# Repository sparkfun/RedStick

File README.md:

**NOTE:** *This product has been retired from our catalog. If you are looking for more up-to-date info, please check out some of these resources to see how other users are still hacking and improving on this product.*
* *[SparkFun Forum](https://forum.sparkfun.com/)*
* *[Comments Here on GitHub](https://github.com/sparkfun/RedStick/issues)*

SparkFun RedStick
========================================

[*SparkFun RedStick (DEV-13741)*](https://www.sparkfun.com/products/13741)

A 328p micro board with boost regulator that runs at 16MHz and has a built in boost regulator for battery usage.

Spawned from the BadgerStick promo.

Repository Contents
-------------------

* **/Documentation** - Data sheets, additional product information
* **/Hardware** - Eagle design files (.brd, .sch)
* **/Production** - Production panel files (.brd)
* **/Software** - Related software for the RedStick

Documentation
--------------
* **[LED Array Library](https://github.com/sparkfun/SparkFun_LED_Array_8x7_Arduino_Library)** - Arduino LED Array library for the RedStick.
* **[Hookup Guide](https://learn.sparkfun.com/tutorials/redstick-hookup-guide)** - Basic hookup guide for the RedStick.
* **[SparkFun Fritzing repo](https://github.com/sparkfun/Fritzing_Parts)** - Fritzing diagrams for SparkFun products.
* **[SparkFun 3D Model repo](https://github.com/sparkfun/3D_Models)** - 3D models of SparkFun products. 

Version History
---------------
* [V_1.0](https://github.com/sparkfun/RedStick/tree/V_1.0) - Product release version

License Information
-------------------

This product is _**open source**_! 

Please review the LICENSE.md file for license information. 

If you have any questions or concerns on licensing, please contact techsupport@sparkfun.com.

Distributed as-is; no warranty is given.

- Your friends at SparkFun.

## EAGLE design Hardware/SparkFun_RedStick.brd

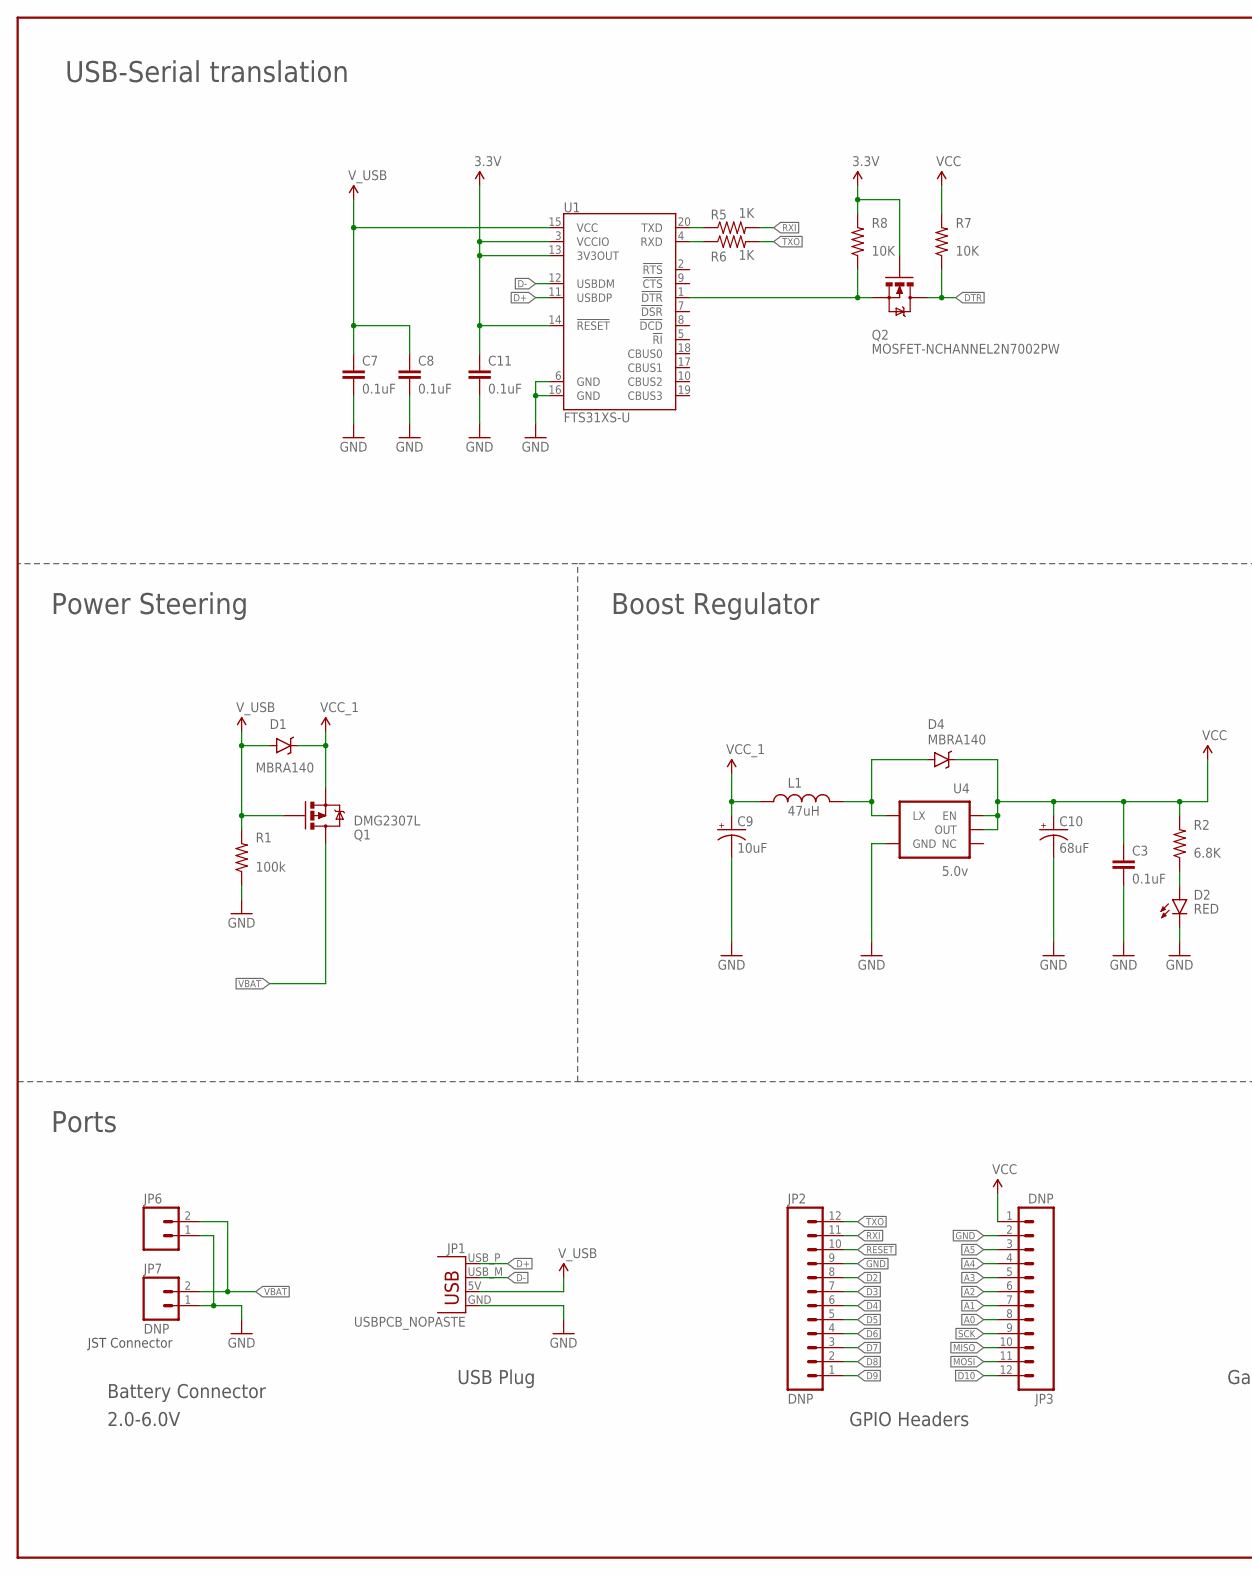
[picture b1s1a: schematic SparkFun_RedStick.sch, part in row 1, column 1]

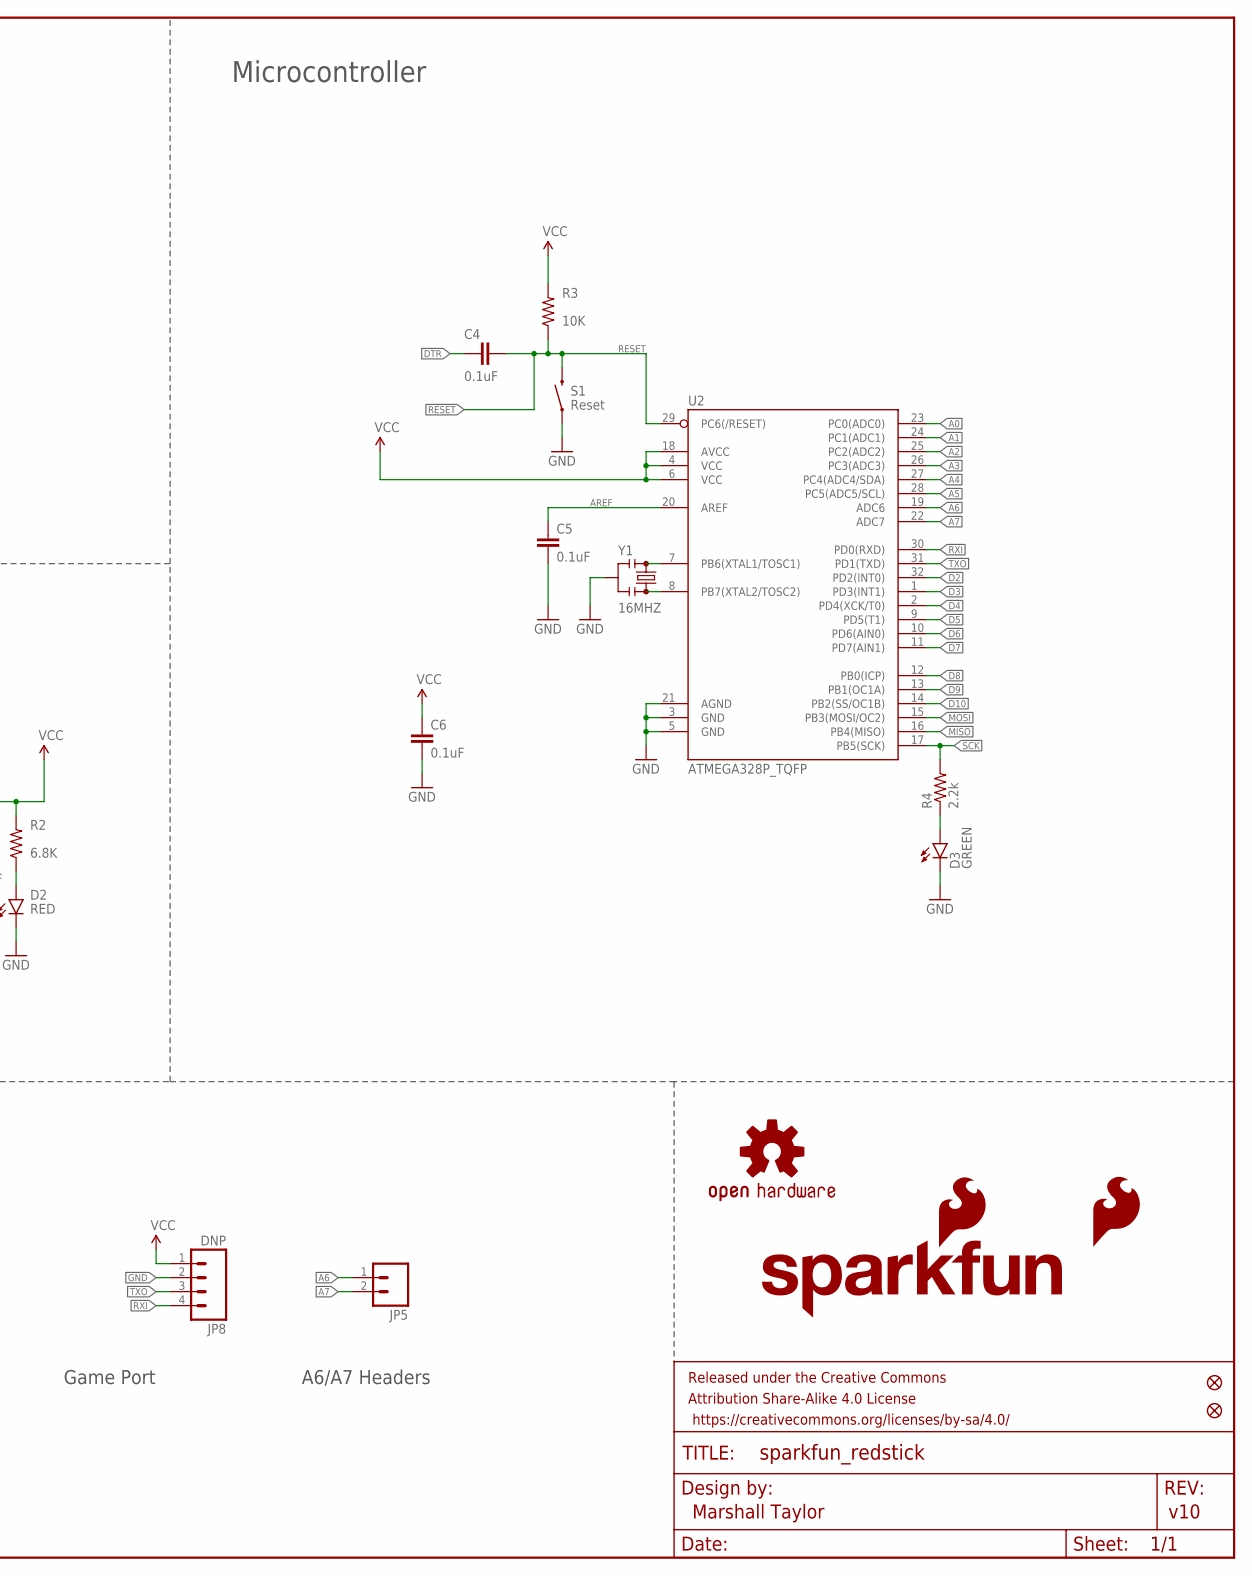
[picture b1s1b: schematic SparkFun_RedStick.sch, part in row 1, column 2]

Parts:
C3, C4, C5, C6, C7, C8, C11: 0.1uF; 0603-CAP
C9: 10uF; EIA3216
C10: 68uF; EIA3528
D1, D4: MBRA140; SMA-DIODE
D2: RED; LED-0603
D3: GREEN; LED-0603
FID1, FID2: FIDUCIAL1X2; FIDUCIAL-1X2
FRAME2: FRAME-LEDGER; CREATIVE_COMMONS
JP1: USBPCB_NOPASTE; USB-A-PCB-NOPASTE
JP2, JP3: DNP; 1X12_NO_SILK
JP5, JP6: M021X02_NO_SILK; 1X02_NO_SILK
JP7: DNP; JST-2-PTH
JP8: DNP; 1X04_NO_SILK_ALL_ROUND
L1: 47uH; CR54
LOGO1: SFE_LOGO_FLAME.1_INCH; SFE_LOGO_FLAME_.1
LOGO2: OSHW-LOGOS; OSHW-LOGO-S
Q1: DMG2307L; SOT23-3
Q2: MOSFET-NCHANNEL2N7002PW; SOT323
R1: 100k; 0603-RES
R2: 6.8K; 0603-RES
R3, R7, R8: 10K; 0603-RES
R4: 2.2k; 0603-RES
R5, R6: 1K; 0603-RES
S1: SWITCH-MOMENTARY-2SMD-REDUNDANT; TACTILE-SWITCH-SMD
U1: FTS31XS-U; SSOP20_L
U2: ATMEGA328P_TQFP; TQFP32-08
U4: 5.0v; SOT23-5
U$1: SFE_LOGO_NAME_FLAME.1_INCH; SFE_LOGO_NAME_FLAME_.1
Y1: 16MHZ; RESONATOR-SMD

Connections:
3.3V: C11.1, Q2.1 (G), R8.2, U1.3 (VCCIO), U1.13 (3V3OUT), U1.14 (!RESET)
A0: JP3.8, U2.23 (PC0(ADC0))
A1: JP3.7, U2.24 (PC1(ADC1))
A2: JP3.6, U2.25 (PC2(ADC2))
A3: JP3.5, U2.26 (PC3(ADC3))
A4: JP3.4, U2.27 (PC4(ADC4/SDA))
A5: JP3.3, U2.28 (PC5(ADC5/SCL))
A6: JP5.1, U2.19 (ADC6)
A7: JP5.2, U2.22 (ADC7)
AREF: C5.1, U2.20 (AREF)
D2: JP2.8, U2.32 (PD2(INT0))
D3: JP2.7, U2.1 (PD3(INT1))
D4: JP2.6, U2.2 (PD4(XCK/T0))
D5: JP2.5, U2.9 (PD5(T1))
D6: JP2.4, U2.10 (PD6(AIN0))
D7: JP2.3, U2.11 (PD7(AIN1))
D8: JP2.2, U2.12 (PB0(ICP))
D9: JP2.1, U2.13 (PB1(OC1A))
D10: JP3.12, U2.14 (PB2(SS/OC1B))
D+: JP1.USB_P (D+), U1.11 (USBDP)
D-: JP1.USB_M (D-), U1.12 (USBDM)
DTR: C4.1, Q2.3 (D), R7.1
GND: C3.2, C5.2, C6.2, C7.2, C8.2, C9.C (-), C10.C (-), C11.2, D2.C, D3.C, JP1.GND, JP2.9, JP3.2, JP6.1, JP7.1, JP8.2, R1.1, S1.1, S1.2 (1), U1.6 (GND), U1.16 (GND), U2.3 (GND), U2.5 (GND), U2.21 (AGND), U4.4 (GND), Y1.2
MISO: JP3.10, U2.16 (PB4(MISO))
MOSI: JP3.11, U2.15 (PB3(MOSI/OC2))
unnamed: D3.A, R4.1
unnamed: R5.1, U1.20 (TXD)
unnamed: D2.A, R2.1
unnamed: U2.7 (PB6(XTAL1/TOSC1)), Y1.1
unnamed: U2.8 (PB7(XTAL2/TOSC2)), Y1.3
unnamed: R6.1, U1.4 (RXD)
unnamed: D4.A, L1.P$2 (2), U4.5 (LX)
unnamed: Q2.2 (S), R8.1, U1.1 (!DTR)
RESET: C4.2, JP2.10, R3.1, S1.3 (2), S1.4 (2), U2.29 (PC6(/RESET))
RXI: JP2.11, JP8.4, R5.2, U2.30 (PD0(RXD))
SCK: JP3.9, R4.2, U2.17 (PB5(SCK))
TXO: JP2.12, JP8.3, R6.2, U2.31 (PD1(TXD))
VBAT: JP6.2, JP7.2, Q1.3 (D)
VCC: C3.1, C6.1, C10.A (+), D4.C, JP3.1, JP8.1, R2.2, R3.2, R7.2, U2.4 (VCC), U2.6 (VCC), U2.18 (AVCC), U4.1 (EN), U4.2 (OUT)
VCC_1: C9.A (+), D1.C, L1.P$1 (1), Q1.2 (S)
V_USB: C7.1, C8.1, D1.A, JP1.5V (VBUS), Q1.1 (G), R1.2, U1.15 (VCC)

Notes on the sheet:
USB Plug
GPIO Headers
A6/A7 Headers
Game Port
Battery Connector
JST Connector
Ports
Power Steering
Boost Regulator
USB-Serial translation
Microcontroller
v10
Marshall Taylor
2.0-6.0V

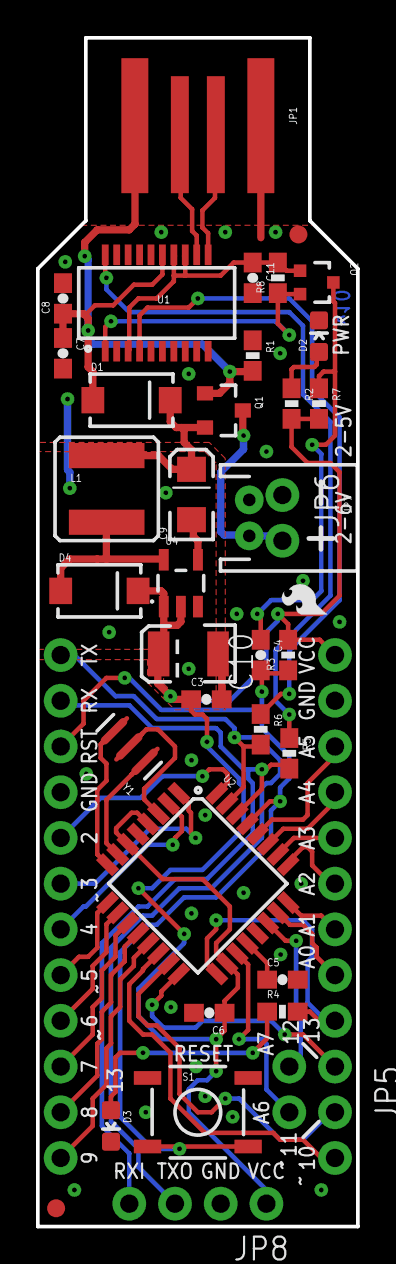
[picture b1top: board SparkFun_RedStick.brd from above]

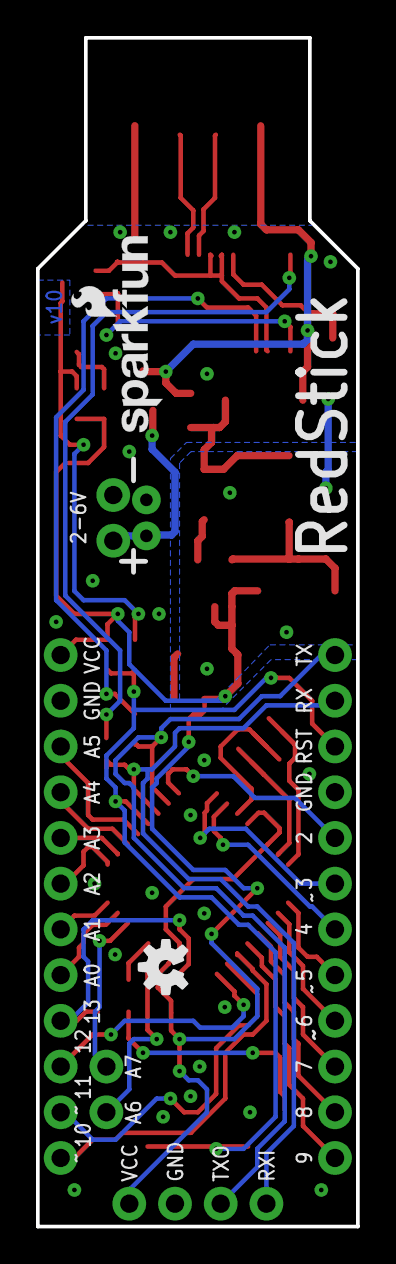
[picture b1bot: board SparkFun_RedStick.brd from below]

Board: 2 copper layers, 17.8 x 66.0 mm, 42 parts (2 on the bottom side), 41 nets.

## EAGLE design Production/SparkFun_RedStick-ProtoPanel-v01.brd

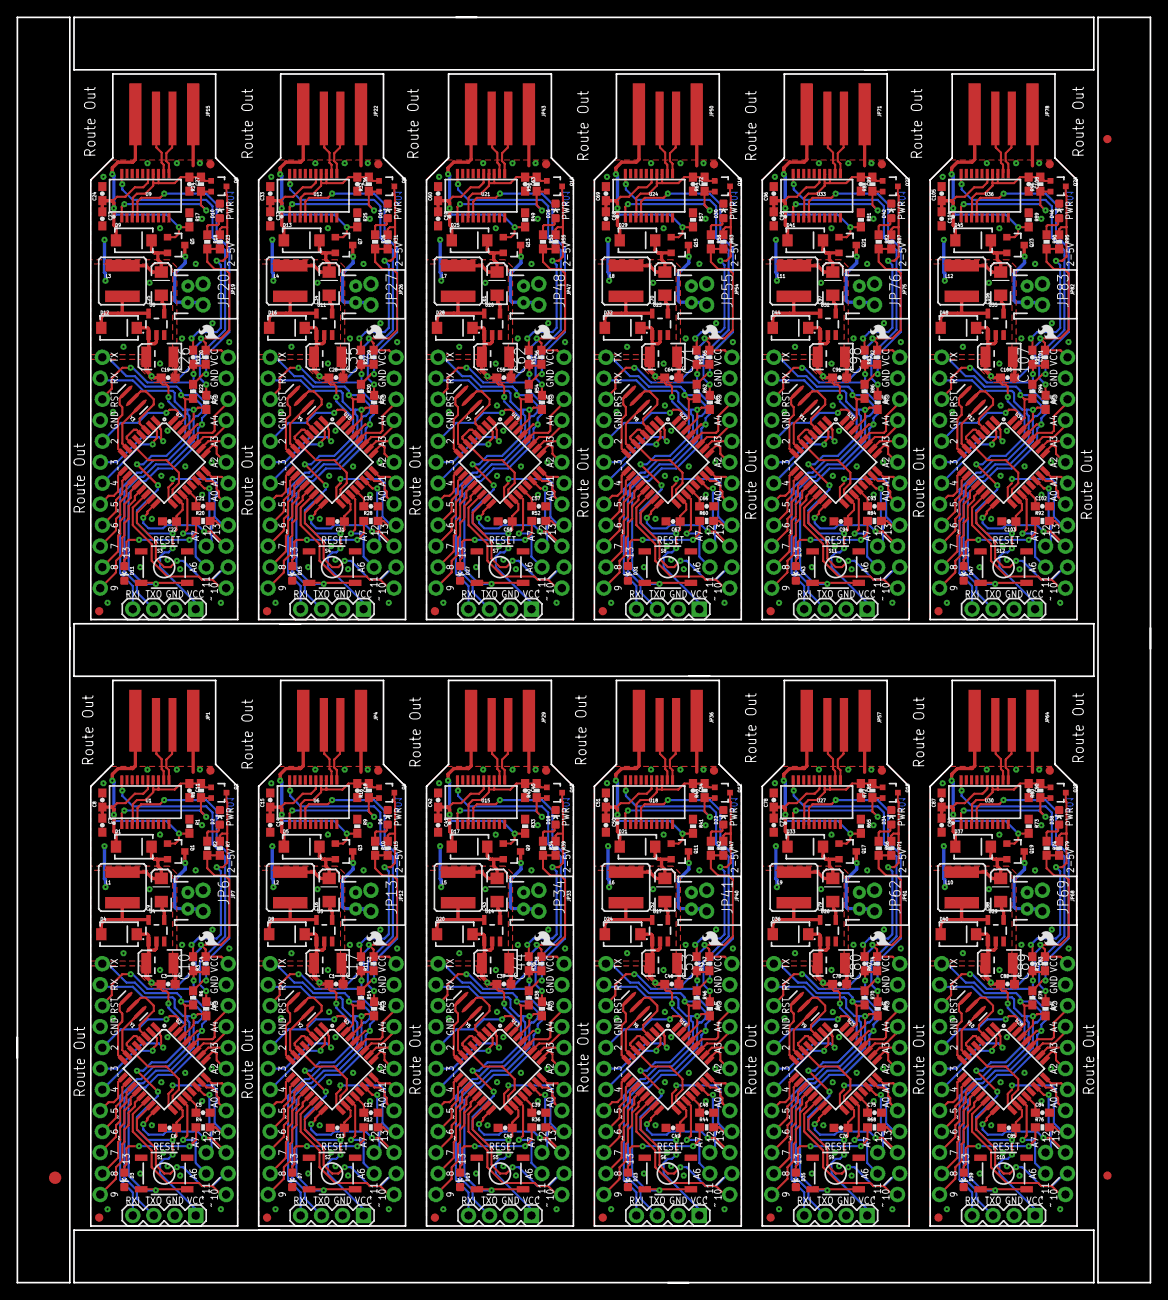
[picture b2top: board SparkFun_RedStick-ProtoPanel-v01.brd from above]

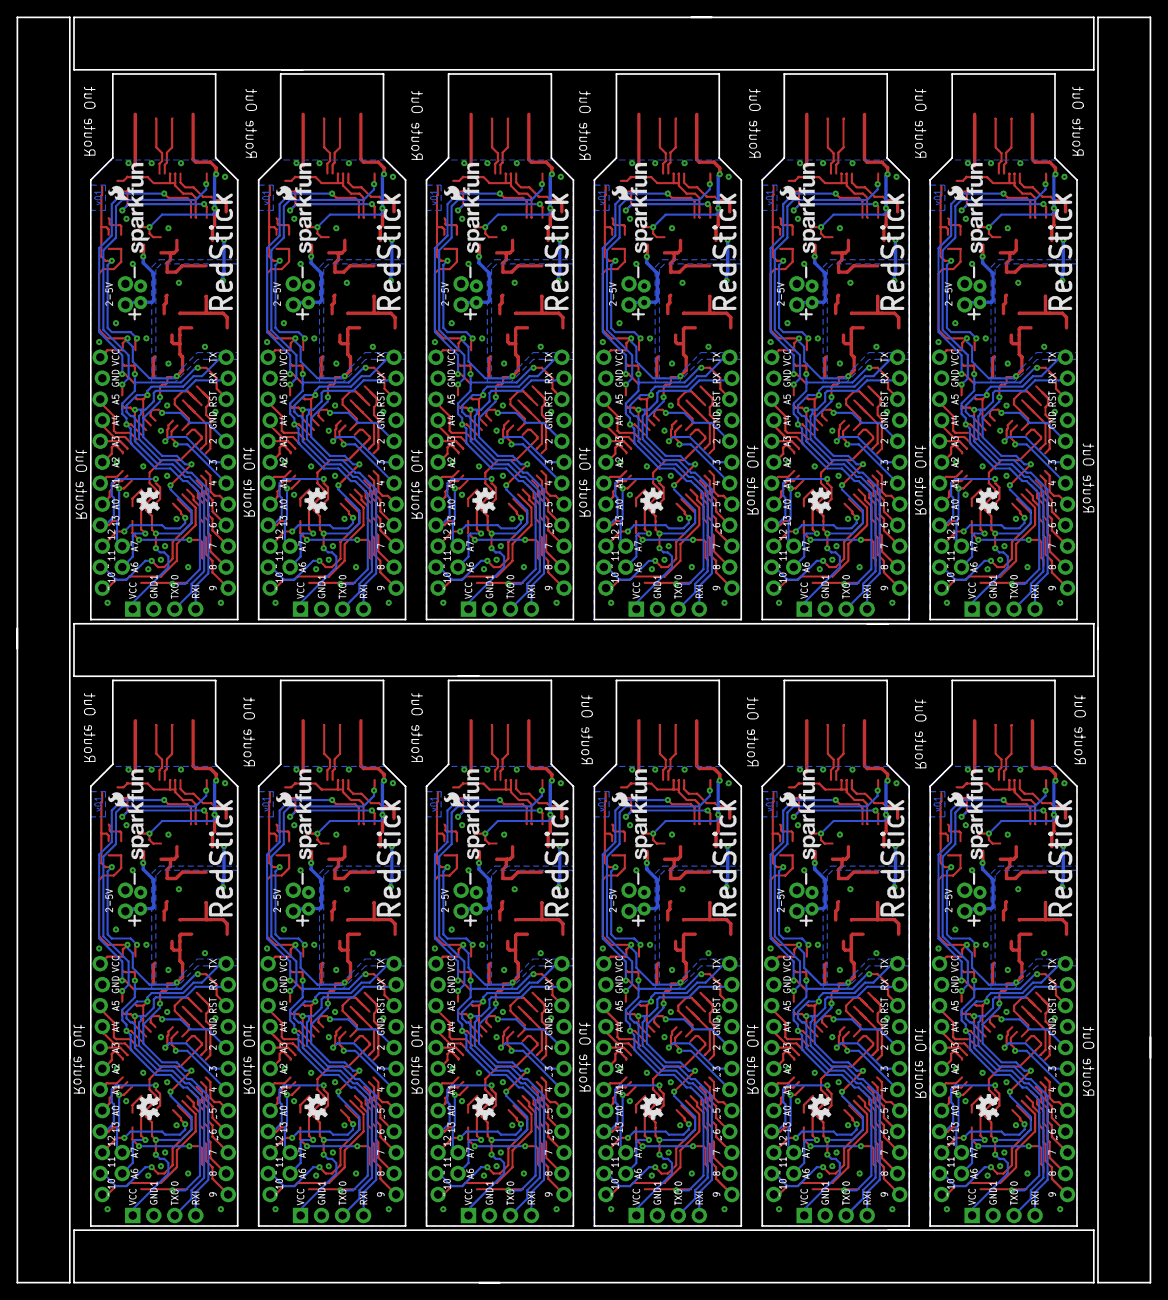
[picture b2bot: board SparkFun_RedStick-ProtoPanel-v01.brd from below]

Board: 2 copper layers, 137.2 x 153.2 mm, 495 parts (24 on the bottom side), 492 nets.

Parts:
C1, C2, C3, C4, C5, C6, C7, C8, C11, C12, C13, C14, C15, C18, C19, C20, C21, C22, C23, C24, C27, C28, C29, C30, C31, C32, C33, C36, C37, C38, C39, C40, C41, C42, C45, C46, C47, C48, C49, C50, C51, C54, C55, C56, C57, C58, C59, C60, C63, C64, C65, C66, C67, C68, C69, C72, C73, C74, C75, C76, C77, C78, C81, C82, C83, C84, C85, C86, C87, C90, C91, C92, C93, C94, C95, C96, C99, C100, C101, C102, C103, C104, C105, C108: 0.1uF; 0603-CAP
C9, C16, C25, C34, C43, C52, C61, C70, C79, C88, C97, C106: 10uF; EIA3216
C10, C17, C26, C35, C44, C53, C62, C71, C80, C89, C98, C107: 68uF; EIA3528
D1, D4, D5, D8, D9, D12, D13, D16, D17, D20, D21, D24, D25, D28, D29, D32, D33, D36, D37, D40, D41, D44, D45, D48: MBRA140; SMA-DIODE
D2, D6, D10, D14, D18, D22, D26, D30, D34, D38, D42, D46: RED; LED-0603
D3, D7, D11, D15, D19, D23, D27, D31, D35, D39, D43, D47: GREEN; LED-0603
E$1: FIDUCIAL-1.5X3
E$7, E$8: FIDUCIAL-1X2
FID1, FID2, FID3, FID4, FID5, FID6, FID7, FID8, FID9, FID10, FID11, FID12, FID13, FID14, FID15, FID16, FID17, FID18, FID19, FID20, FID21, FID22, FID23, FID24: FIDUCIAL1X2; FIDUCIAL-1X2
JP1, JP4, JP15, JP22, JP29, JP36, JP43, JP50, JP57, JP64, JP71, JP78: USBPCB_NOPASTE; USB-A-PCB-NOPASTE
JP2, JP3, JP10, JP11, JP17, JP18, JP24, JP25, JP31, JP32, JP38, JP39, JP45, JP46, JP52, JP53, JP59, JP60, JP66, JP67, JP73, JP74, JP80, JP81: DNP; 1X12_LOCK_NO_SILK
JP5, JP6, JP9, JP13, JP16, JP20, JP23, JP27, JP30, JP34, JP37, JP41, JP44, JP48, JP51, JP55, JP58, JP62, JP65, JP69, JP72, JP76, JP79, JP83: M021X02_NO_SILK; 1X02_NO_SILK
JP7, JP12, JP19, JP26, JP33, JP40, JP47, JP54, JP61, JP68, JP75, JP82: DNP; JST-2-PTH
JP8, JP14, JP21, JP28, JP35, JP42, JP49, JP56, JP63, JP70, JP77, JP84: DNP; 1X04
L1, L2, L3, L4, L5, L6, L7, L8, L9, L10, L11, L12: 47uH; CR54
LOGO1, LOGO3, LOGO5, LOGO7, LOGO9, LOGO11, LOGO13, LOGO15, LOGO17, LOGO19, LOGO21, LOGO23: SFE_LOGO_FLAME.1_INCH; SFE_LOGO_FLAME_.1
LOGO2, LOGO4, LOGO6, LOGO8, LOGO10, LOGO12, LOGO14, LOGO16, LOGO18, LOGO20, LOGO22, LOGO24: OSHW-LOGOS; OSHW-LOGO-S
Q1, Q3, Q5, Q7, Q9, Q11, Q13, Q15, Q17, Q19, Q21, Q23: DMG2307L; SOT23-3
Q2, Q4, Q6, Q8, Q10, Q12, Q14, Q16, Q18, Q20, Q22, Q24: MOSFET-NCHANNEL2N7002PW; SOT323
R1, R9, R17, R25, R33, R41, R49, R57, R65, R73, R81, R89: 100k; 0603-RES
R2, R3, R7, R8, R10, R11, R15, R16, R18, R19, R23, R24, R26, R27, R31, R32, R34, R35, R39, R40, R42, R43, R47, R48, R50, R51, R55, R56, R58, R59, R63, R64, R66, R67, R71, R72, R74, R75, R79, R80, R82, R83, R87, R88, R90, R91, R95, R96: 10K; 0603-RES
R4, R12, R20, R28, R36, R44, R52, R60, R68, R76, R84, R92: 330; 0603-RES
R5, R6, R13, R14, R21, R22, R29, R30, R37, R38, R45, R46, R53, R54, R61, R62, R69, R70, R77, R78, R85, R86, R93, R94: 1K; 0603-RES
S1, S2, S3, S4, S5, S6, S7, S8, S9, S10, S11, S12: SWITCH-MOMENTARY-2SMD-REDUNDANT; TACTILE-SWITCH-SMD
U1, U6, U9, U12, U15, U18, U21, U24, U27, U30, U33, U36: FTS31XS-U; SSOP20_L
U2, U3, U7, U10, U13, U16, U19, U22, U25, U28, U31, U34: ATMEGA328P_TQFP; TQFP32-08
U4, U5, U8, U11, U14, U17, U20, U23, U26, U29, U32, U35: 5.0v; SOT23-5
U$1, U$2, U$3, U$4, U$5, U$6, U$7, U$8, U$9, U$10, U$11, U$12: SFE_LOGO_NAME_FLAME.1_INCH; SFE_LOGO_NAME_FLAME_.1
Y1, Y2, Y3, Y4, Y5, Y6, Y7, Y8, Y9, Y10, Y11, Y12: 16MHZ; RESONATOR-SMD

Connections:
3.3V: C11.1, Q2.1, R8.2, U1.3, U1.13, U1.14
3.3V1: C18.1, Q4.1, R16.2, U6.3, U6.13, U6.14
3.3V2: C27.1, Q6.1, R24.2, U9.3, U9.13, U9.14
3.3V3: C36.1, Q8.1, R32.2, U12.3, U12.13, U12.14
3.3V4: C45.1, Q10.1, R40.2, U15.3, U15.13, U15.14
3.3V5: C54.1, Q12.1, R48.2, U18.3, U18.13, U18.14
3.3V6: C63.1, Q14.1, R56.2, U21.3, U21.13, U21.14
3.3V7: C72.1, Q16.1, R64.2, U24.3, U24.13, U24.14
3.3V8: C81.1, Q18.1, R72.2, U27.3, U27.13, U27.14
3.3V9: C90.1, Q20.1, R80.2, U30.3, U30.13, U30.14
3.3V10: C99.1, Q22.1, R88.2, U33.3, U33.13, U33.14
3.3V11: C108.1, Q24.1, R96.2, U36.3, U36.13, U36.14
A0: JP3.8, U2.23
A1: JP3.7, U2.24
A2: JP3.6, U2.25
A3: JP3.5, U2.26
A4: JP3.4, U2.27
A5: JP3.3, U2.28
A6: JP5.1, U2.19
A7: JP5.2, U2.22
A8: JP10.8, U3.23
A9: JP10.7, U3.24
A10: JP10.6, U3.25
A11: JP10.5, U3.26
A12: JP10.4, U3.27
A13: JP10.3, U3.28
A14: JP9.1, U3.19
A15: JP9.2, U3.22
A16: JP17.8, U7.23
A17: JP17.7, U7.24
A18: JP17.6, U7.25
A19: JP17.5, U7.26
A20: JP17.4, U7.27
A21: JP17.3, U7.28
A22: JP16.1, U7.19
A23: JP16.2, U7.22
A24: JP24.8, U10.23
A25: JP24.7, U10.24
A26: JP24.6, U10.25
A27: JP24.5, U10.26
A28: JP24.4, U10.27
A29: JP24.3, U10.28
A30: JP23.1, U10.19
A31: JP23.2, U10.22
A32: JP31.8, U13.23
A33: JP31.7, U13.24
A34: JP31.6, U13.25
A35: JP31.5, U13.26
A36: JP31.4, U13.27
A37: JP31.3, U13.28
A38: JP30.1, U13.19
A39: JP30.2, U13.22
A40: JP38.8, U16.23
A41: JP38.7, U16.24
A42: JP38.6, U16.25
A43: JP38.5, U16.26
A44: JP38.4, U16.27
A45: JP38.3, U16.28
A46: JP37.1, U16.19
A47: JP37.2, U16.22
A48: JP45.8, U19.23
A49: JP45.7, U19.24
A50: JP45.6, U19.25
A51: JP45.5, U19.26
A52: JP45.4, U19.27
A53: JP45.3, U19.28
A54: JP44.1, U19.19
A55: JP44.2, U19.22
A56: JP52.8, U22.23
A57: JP52.7, U22.24
A58: JP52.6, U22.25
A59: JP52.5, U22.26
A60: JP52.4, U22.27
A61: JP52.3, U22.28
A62: JP51.1, U22.19
A63: JP51.2, U22.22
A64: JP59.8, U25.23
A65: JP59.7, U25.24
A66: JP59.6, U25.25
A67: JP59.5, U25.26
A68: JP59.4, U25.27
A69: JP59.3, U25.28
A70: JP58.1, U25.19
A71: JP58.2, U25.22
A72: JP66.8, U28.23
A73: JP66.7, U28.24
A74: JP66.6, U28.25
A75: JP66.5, U28.26
A76: JP66.4, U28.27
A77: JP66.3, U28.28
A78: JP65.1, U28.19
A79: JP65.2, U28.22
A80: JP73.8, U31.23
A81: JP73.7, U31.24
A82: JP73.6, U31.25
A83: JP73.5, U31.26
A84: JP73.4, U31.27
A85: JP73.3, U31.28
A86: JP72.1, U31.19
A87: JP72.2, U31.22
A88: JP80.8, U34.23
A89: JP80.7, U34.24
A90: JP80.6, U34.25
A91: JP80.5, U34.26
A92: JP80.4, U34.27
A93: JP80.3, U34.28
A94: JP79.1, U34.19
A95: JP79.2, U34.22
AREF: C5.1, U2.20
AREF1: C12.1, U3.20
AREF2: C21.1, U7.20
AREF3: C30.1, U10.20
AREF4: C39.1, U13.20
AREF5: C48.1, U16.20
AREF6: C57.1, U19.20
AREF7: C66.1, U22.20
AREF8: C75.1, U25.20
AREF9: C84.1, U28.20
AREF10: C93.1, U31.20
AREF11: C102.1, U34.20
D1: JP11.8, U3.32
D2: JP2.8, U2.32
D3: JP2.7, U2.1
D4: JP2.6, U2.2
D5: JP2.5, U2.9
D6: JP2.4, U2.10
D7: JP2.3, U2.11
D8: JP2.2, U2.12
D9: JP2.1, U2.13
D10: JP3.12, U2.14
D11: JP11.7, U3.1
D12: JP11.6, U3.2
D13: JP11.5, U3.9
D14: JP11.4, U3.10
D15: JP11.3, U3.11
D16: JP11.2, U3.12
D17: JP11.1, U3.13
D18: JP10.12, U3.14
D19: JP18.8, U7.32
D20: JP18.7, U7.1
D21: JP18.6, U7.2
D22: JP18.5, U7.9
D23: JP18.4, U7.10
D24: JP18.3, U7.11
D25: JP18.2, U7.12
D26: JP18.1, U7.13
D27: JP17.12, U7.14
D28: JP25.8, U10.32
D29: JP25.7, U10.1
D30: JP25.6, U10.2
D31: JP25.5, U10.9
D32: JP25.4, U10.10
D33: JP25.3, U10.11
D34: JP25.2, U10.12
D35: JP25.1, U10.13
D36: JP24.12, U10.14
D37: JP32.8, U13.32
D38: JP32.7, U13.1
D39: JP32.6, U13.2
D40: JP32.5, U13.9
D41: JP32.4, U13.10
D42: JP32.3, U13.11
D43: JP32.2, U13.12
D44: JP32.1, U13.13
D45: JP31.12, U13.14
D46: JP39.8, U16.32
D47: JP39.7, U16.1
D48: JP39.6, U16.2
D49: JP39.5, U16.9
D50: JP39.4, U16.10
D51: JP39.3, U16.11
D52: JP39.2, U16.12
D53: JP39.1, U16.13
D54: JP38.12, U16.14
D55: JP46.8, U19.32
D56: JP46.7, U19.1
D57: JP46.6, U19.2
D58: JP46.5, U19.9
D59: JP46.4, U19.10
D60: JP46.3, U19.11
D61: JP46.2, U19.12
D62: JP46.1, U19.13
D63: JP45.12, U19.14
D64: JP53.8, U22.32
D65: JP53.7, U22.1
D66: JP53.6, U22.2
D67: JP53.5, U22.9
D68: JP53.4, U22.10
D69: JP53.3, U22.11
D70: JP53.2, U22.12
D71: JP53.1, U22.13
D72: JP52.12, U22.14
D73: JP60.8, U25.32
D74: JP60.7, U25.1
D75: JP60.6, U25.2
D76: JP60.5, U25.9
D77: JP60.4, U25.10
D78: JP60.3, U25.11
D79: JP60.2, U25.12
D80: JP60.1, U25.13
D81: JP59.12, U25.14
D82: JP67.8, U28.32
D83: JP67.7, U28.1
D84: JP67.6, U28.2
D85: JP67.5, U28.9
D86: JP67.4, U28.10
D87: JP67.3, U28.11
D88: JP67.2, U28.12
D89: JP67.1, U28.13
D90: JP66.12, U28.14
D91: JP74.8, U31.32
D92: JP74.7, U31.1
D93: JP74.6, U31.2
D94: JP74.5, U31.9
D95: JP74.4, U31.10
D96: JP74.3, U31.11
D97: JP74.2, U31.12
D98: JP74.1, U31.13
D99: JP73.12, U31.14
D100: JP81.8, U34.32
D101: JP81.7, U34.1
D102: JP81.6, U34.2
D103: JP81.5, U34.9
D104: JP81.4, U34.10
D105: JP81.3, U34.11
D106: JP81.2, U34.12
D107: JP81.1, U34.13
D108: JP80.12, U34.14
D+: JP1.USB_P, U1.11
D+1: JP4.USB_P, U6.11
D+2: JP15.USB_P, U9.11
D+3: JP22.USB_P, U12.11
D+4: JP29.USB_P, U15.11
D+5: JP36.USB_P, U18.11
D+6: JP43.USB_P, U21.11
D+7: JP50.USB_P, U24.11
D+8: JP57.USB_P, U27.11
D+9: JP64.USB_P, U30.11
D+10: JP71.USB_P, U33.11
D+11: JP78.USB_P, U36.11
D-: JP1.USB_M, U1.12
D-1: JP4.USB_M, U6.12
D-2: JP15.USB_M, U9.12
D-3: JP22.USB_M, U12.12
D-4: JP29.USB_M, U15.12
D-5: JP36.USB_M, U18.12
D-6: JP43.USB_M, U21.12
D-7: JP50.USB_M, U24.12
D-8: JP57.USB_M, U27.12
D-9: JP64.USB_M, U30.12
D-10: JP71.USB_M, U33.12
D-11: JP78.USB_M, U36.12
DTR: C4.1, Q2.3, R7.1
DTR1: C2.1, Q4.3, R15.1
DTR2: C20.1, Q6.3, R23.1
DTR3: C29.1, Q8.3, R31.1
DTR4: C38.1, Q10.3, R39.1
DTR5: C47.1, Q12.3, R47.1
DTR6: C56.1, Q14.3, R55.1
DTR7: C65.1, Q16.3, R63.1
DTR8: C74.1, Q18.3, R71.1
DTR9: C83.1, Q20.3, R79.1
DTR10: C92.1, Q22.3, R87.1
DTR11: C101.1, Q24.3, R95.1
GND: C3.2, C5.2, C6.2, C7.2, C8.2, C9.C, C10.C, C11.2, D2.C, D3.C, JP1.GND, JP2.9, JP3.2, JP6.1, JP7.1, JP8.2, R1.1, S1.1, S1.2, U1.6, U1.16, U2.3, U2.5, U2.21, U4.4, Y1.2
GND1: C1.2, C12.2, C13.2, C14.2, C15.2, C16.C, C17.C, C18.2, D6.C, D7.C, JP4.GND, JP10.2, JP11.9, JP12.1, JP13.1, JP14.2, R9.1, S2.1, S2.2, U3.3, U3.5, U3.21, U5.4, U6.6, U6.16, Y2.2
GND2: C19.2, C21.2, C22.2, C23.2, C24.2, C25.C, C26.C, C27.2, D10.C, D11.C, JP15.GND, JP17.2, JP18.9, JP19.1, JP20.1, JP21.2, R17.1, S3.1, S3.2, U7.3, U7.5, U7.21, U8.4, U9.6, U9.16, Y3.2
GND3: C28.2, C30.2, C31.2, C32.2, C33.2, C34.C, C35.C, C36.2, D14.C, D15.C, JP22.GND, JP24.2, JP25.9, JP26.1, JP27.1, JP28.2, R25.1, S4.1, S4.2, U10.3, U10.5, U10.21, U11.4, U12.6, U12.16, Y4.2
GND4: C37.2, C39.2, C40.2, C41.2, C42.2, C43.C, C44.C, C45.2, D18.C, D19.C, JP29.GND, JP31.2, JP32.9, JP33.1, JP34.1, JP35.2, R33.1, S5.1, S5.2, U13.3, U13.5, U13.21, U14.4, U15.6, U15.16, Y5.2
GND5: C46.2, C48.2, C49.2, C50.2, C51.2, C52.C, C53.C, C54.2, D22.C, D23.C, JP36.GND, JP38.2, JP39.9, JP40.1, JP41.1, JP42.2, R41.1, S6.1, S6.2, U16.3, U16.5, U16.21, U17.4, U18.6, U18.16, Y6.2
GND6: C55.2, C57.2, C58.2, C59.2, C60.2, C61.C, C62.C, C63.2, D26.C, D27.C, JP43.GND, JP45.2, JP46.9, JP47.1, JP48.1, JP49.2, R49.1, S7.1, S7.2, U19.3, U19.5, U19.21, U20.4, U21.6, U21.16, Y7.2
GND7: C64.2, C66.2, C67.2, C68.2, C69.2, C70.C, C71.C, C72.2, D30.C, D31.C, JP50.GND, JP52.2, JP53.9, JP54.1, JP55.1, JP56.2, R57.1, S8.1, S8.2, U22.3, U22.5, U22.21, U23.4, U24.6, U24.16, Y8.2
GND8: C73.2, C75.2, C76.2, C77.2, C78.2, C79.C, C80.C, C81.2, D34.C, D35.C, JP57.GND, JP59.2, JP60.9, JP61.1, JP62.1, JP63.2, R65.1, S9.1, S9.2, U25.3, U25.5, U25.21, U26.4, U27.6, U27.16, Y9.2
GND9: C82.2, C84.2, C85.2, C86.2, C87.2, C88.C, C89.C, C90.2, D38.C, D39.C, JP64.GND, JP66.2, JP67.9, JP68.1, JP69.1, JP70.2, R73.1, S10.1, S10.2, U28.3, U28.5, U28.21, U29.4, U30.6, U30.16, Y10.2
GND10: C91.2, C93.2, C94.2, C95.2, C96.2, C97.C, C98.C, C99.2, D42.C, D43.C, JP71.GND, JP73.2, JP74.9, JP75.1, JP76.1, JP77.2, R81.1, S11.1, S11.2, U31.3, U31.5, U31.21, U32.4, U33.6, U33.16, Y11.2
GND11: C100.2, C102.2, C103.2, C104.2, C105.2, C106.C, C107.C, C108.2, D46.C, D47.C, JP78.GND, JP80.2, JP81.9, JP82.1, JP83.1, JP84.2, R89.1, S12.1, S12.2, U34.3, U34.5, U34.21, U35.4, U36.6, U36.16, Y12.2
MISO: JP3.10, U2.16
MISO1: JP10.10, U3.16
MISO2: JP17.10, U7.16
MISO3: JP24.10, U10.16
MISO4: JP31.10, U13.16
MISO5: JP38.10, U16.16
MISO6: JP45.10, U19.16
MISO7: JP52.10, U22.16
MISO8: JP59.10, U25.16
MISO9: JP66.10, U28.16
MISO10: JP73.10, U31.16
MISO11: JP80.10, U34.16
MOSI: JP3.11, U2.15
MOSI1: JP10.11, U3.15
MOSI2: JP17.11, U7.15
MOSI3: JP24.11, U10.15
MOSI4: JP31.11, U13.15
MOSI5: JP38.11, U16.15
MOSI6: JP45.11, U19.15
MOSI7: JP52.11, U22.15
MOSI8: JP59.11, U25.15
MOSI9: JP66.11, U28.15
MOSI10: JP73.11, U31.15
MOSI11: JP80.11, U34.15
unnamed: D3.A, R4.1
unnamed: D7.A, R12.1
unnamed: R5.1, U1.20
unnamed: D2.A, R2.1
unnamed: U2.7, Y1.1
unnamed: U2.8, Y1.3
unnamed: R6.1, U1.4
unnamed: D4.A, L1.P$2, U4.5
unnamed: Q2.2, R8.1, U1.1
unnamed: U3.7, Y2.1
unnamed: U3.8, Y2.3
unnamed: R13.1, U6.20
unnamed: R14.1, U6.4
unnamed: D8.A, L2.P$2, U5.5
unnamed: D6.A, R10.1
unnamed: Q4.2, R16.1, U6.1
unnamed: D11.A, R20.1
unnamed: U7.7, Y3.1
unnamed: U7.8, Y3.3
unnamed: R21.1, U9.20
unnamed: R22.1, U9.4
unnamed: D12.A, L3.P$2, U8.5
unnamed: D10.A, R18.1
unnamed: Q6.2, R24.1, U9.1
unnamed: D15.A, R28.1
unnamed: U10.7, Y4.1
unnamed: U10.8, Y4.3
unnamed: R29.1, U12.20
unnamed: R30.1, U12.4
unnamed: D16.A, L4.P$2, U11.5
unnamed: D14.A, R26.1
unnamed: Q8.2, R32.1, U12.1
unnamed: D19.A, R36.1
unnamed: U13.7, Y5.1
unnamed: U13.8, Y5.3
unnamed: R37.1, U15.20
unnamed: R38.1, U15.4
unnamed: D20.A, L5.P$2, U14.5
unnamed: D18.A, R34.1
unnamed: Q10.2, R40.1, U15.1
unnamed: D23.A, R44.1
unnamed: U16.7, Y6.1
unnamed: U16.8, Y6.3
unnamed: R45.1, U18.20
unnamed: R46.1, U18.4
unnamed: D24.A, L6.P$2, U17.5
unnamed: D22.A, R42.1
unnamed: Q12.2, R48.1, U18.1
unnamed: D27.A, R52.1
unnamed: U19.7, Y7.1
unnamed: U19.8, Y7.3
unnamed: R53.1, U21.20
unnamed: R54.1, U21.4
unnamed: D28.A, L7.P$2, U20.5
unnamed: D26.A, R50.1
unnamed: Q14.2, R56.1, U21.1
unnamed: D31.A, R60.1
unnamed: U22.7, Y8.1
unnamed: U22.8, Y8.3
unnamed: R61.1, U24.20
unnamed: R62.1, U24.4
unnamed: D32.A, L8.P$2, U23.5
unnamed: D30.A, R58.1
unnamed: Q16.2, R64.1, U24.1
unnamed: D35.A, R68.1
unnamed: U25.7, Y9.1
unnamed: U25.8, Y9.3
unnamed: R69.1, U27.20
unnamed: R70.1, U27.4
unnamed: D36.A, L9.P$2, U26.5
unnamed: D34.A, R66.1
unnamed: Q18.2, R72.1, U27.1
unnamed: D39.A, R76.1
unnamed: U28.7, Y10.1
unnamed: U28.8, Y10.3
unnamed: R77.1, U30.20
unnamed: R78.1, U30.4
unnamed: D40.A, L10.P$2, U29.5
unnamed: D38.A, R74.1
unnamed: Q20.2, R80.1, U30.1
unnamed: D43.A, R84.1
unnamed: U31.7, Y11.1
unnamed: U31.8, Y11.3
unnamed: R85.1, U33.20
unnamed: R86.1, U33.4
unnamed: D44.A, L11.P$2, U32.5
unnamed: D42.A, R82.1
unnamed: Q22.2, R88.1, U33.1
unnamed: D47.A, R92.1
unnamed: U34.7, Y12.1
unnamed: U34.8, Y12.3
unnamed: R93.1, U36.20
unnamed: R94.1, U36.4
unnamed: D48.A, L12.P$2, U35.5
unnamed: D46.A, R90.1
unnamed: Q24.2, R96.1, U36.1
RESET: C4.2, JP2.10, R3.1, S1.3, S1.4, U2.29
RESET1: C2.2, JP11.10, R11.1, S2.3, S2.4, U3.29
RESET2: C20.2, JP18.10, R19.1, S3.3, S3.4, U7.29
RESET3: C29.2, JP25.10, R27.1, S4.3, S4.4, U10.29
RESET4: C38.2, JP32.10, R35.1, S5.3, S5.4, U13.29
RESET5: C47.2, JP39.10, R43.1, S6.3, S6.4, U16.29
RESET6: C56.2, JP46.10, R51.1, S7.3, S7.4, U19.29
RESET7: C65.2, JP53.10, R59.1, S8.3, S8.4, U22.29
RESET8: C74.2, JP60.10, R67.1, S9.3, S9.4, U25.29
RESET9: C83.2, JP67.10, R75.1, S10.3, S10.4, U28.29
RESET10: C92.2, JP74.10, R83.1, S11.3, S11.4, U31.29
RESET11: C101.2, JP81.10, R91.1, S12.3, S12.4, U34.29
RXI: JP2.11, JP8.4, R5.2, U2.30
RXI1: JP11.11, JP14.4, R13.2, U3.30
RXI2: JP18.11, JP21.4, R21.2, U7.30
RXI3: JP25.11, JP28.4, R29.2, U10.30
RXI4: JP32.11, JP35.4, R37.2, U13.30
RXI5: JP39.11, JP42.4, R45.2, U16.30
RXI6: JP46.11, JP49.4, R53.2, U19.30
RXI7: JP53.11, JP56.4, R61.2, U22.30
RXI8: JP60.11, JP63.4, R69.2, U25.30
RXI9: JP67.11, JP70.4, R77.2, U28.30
RXI10: JP74.11, JP77.4, R85.2, U31.30
RXI11: JP81.11, JP84.4, R93.2, U34.30
SCK: JP3.9, R4.2, U2.17
SCK1: JP10.9, R12.2, U3.17
SCK2: JP17.9, R20.2, U7.17
SCK3: JP24.9, R28.2, U10.17
SCK4: JP31.9, R36.2, U13.17
SCK5: JP38.9, R44.2, U16.17
SCK6: JP45.9, R52.2, U19.17
SCK7: JP52.9, R60.2, U22.17
SCK8: JP59.9, R68.2, U25.17
SCK9: JP66.9, R76.2, U28.17
SCK10: JP73.9, R84.2, U31.17
SCK11: JP80.9, R92.2, U34.17
TXO: JP2.12, JP8.3, R6.2, U2.31
TXO1: JP11.12, JP14.3, R14.2, U3.31
TXO2: JP18.12, JP21.3, R22.2, U7.31
TXO3: JP25.12, JP28.3, R30.2, U10.31
TXO4: JP32.12, JP35.3, R38.2, U13.31
TXO5: JP39.12, JP42.3, R46.2, U16.31
TXO6: JP46.12, JP49.3, R54.2, U19.31
TXO7: JP53.12, JP56.3, R62.2, U22.31
TXO8: JP60.12, JP63.3, R70.2, U25.31
TXO9: JP67.12, JP70.3, R78.2, U28.31
TXO10: JP74.12, JP77.3, R86.2, U31.31
TXO11: JP81.12, JP84.3, R94.2, U34.31
VBAT: JP6.2, JP7.2, Q1.3
VBAT1: JP12.2, JP13.2, Q3.3
VBAT2: JP19.2, JP20.2, Q5.3
VBAT3: JP26.2, JP27.2, Q7.3
VBAT4: JP33.2, JP34.2, Q9.3
VBAT5: JP40.2, JP41.2, Q11.3
VBAT6: JP47.2, JP48.2, Q13.3
VBAT7: JP54.2, JP55.2, Q15.3
VBAT8: JP61.2, JP62.2, Q17.3
VBAT9: JP68.2, JP69.2, Q19.3
VBAT10: JP75.2, JP76.2, Q21.3
VBAT11: JP82.2, JP83.2, Q23.3
VCC: C3.1, C6.1, C10.A, D4.C, JP3.1, JP8.1, R2.2, R3.2, R7.2, U2.4, U2.6, U2.18, U4.1, U4.2
VCC1: C1.1, C13.1, C17.A, D8.C, JP10.1, JP14.1, R10.2, R11.2, R15.2, U3.4, U3.6, U3.18, U5.1, U5.2
VCC2: C19.1, C22.1, C26.A, D12.C, JP17.1, JP21.1, R18.2, R19.2, R23.2, U7.4, U7.6, U7.18, U8.1, U8.2
VCC3: C28.1, C31.1, C35.A, D16.C, JP24.1, JP28.1, R26.2, R27.2, R31.2, U10.4, U10.6, U10.18, U11.1, U11.2
VCC4: C37.1, C40.1, C44.A, D20.C, JP31.1, JP35.1, R34.2, R35.2, R39.2, U13.4, U13.6, U13.18, U14.1, U14.2
VCC5: C46.1, C49.1, C53.A, D24.C, JP38.1, JP42.1, R42.2, R43.2, R47.2, U16.4, U16.6, U16.18, U17.1, U17.2
VCC6: C55.1, C58.1, C62.A, D28.C, JP45.1, JP49.1, R50.2, R51.2, R55.2, U19.4, U19.6, U19.18, U20.1, U20.2
VCC7: C64.1, C67.1, C71.A, D32.C, JP52.1, JP56.1, R58.2, R59.2, R63.2, U22.4, U22.6, U22.18, U23.1, U23.2
VCC8: C73.1, C76.1, C80.A, D36.C, JP59.1, JP63.1, R66.2, R67.2, R71.2, U25.4, U25.6, U25.18, U26.1, U26.2
VCC9: C82.1, C85.1, C89.A, D40.C, JP66.1, JP70.1, R74.2, R75.2, R79.2, U28.4, U28.6, U28.18, U29.1, U29.2
VCC10: C91.1, C94.1, C98.A, D44.C, JP73.1, JP77.1, R82.2, R83.2, R87.2, U31.4, U31.6, U31.18, U32.1, U32.2
VCC11: C100.1, C103.1, C107.A, D48.C, JP80.1, JP84.1, R90.2, R91.2, R95.2, U34.4, U34.6, U34.18, U35.1, U35.2
VCC_1: C9.A, D1.C, L1.P$1, Q1.2
VCC_2: C16.A, D5.C, L2.P$1, Q3.2
VCC_3: C25.A, D9.C, L3.P$1, Q5.2
VCC_4: C34.A, D13.C, L4.P$1, Q7.2
VCC_5: C43.A, D17.C, L5.P$1, Q9.2
VCC_6: C52.A, D21.C, L6.P$1, Q11.2
VCC_7: C61.A, D25.C, L7.P$1, Q13.2
VCC_8: C70.A, D29.C, L8.P$1, Q15.2
VCC_9: C79.A, D33.C, L9.P$1, Q17.2
VCC_10: C88.A, D37.C, L10.P$1, Q19.2
VCC_11: C97.A, D41.C, L11.P$1, Q21.2
VCC_12: C106.A, D45.C, L12.P$1, Q23.2
V_USB: C7.1, C8.1, D1.A, JP1.5V, Q1.1, R1.2, U1.15
V_USB1: C14.1, C15.1, D5.A, JP4.5V, Q3.1, R9.2, U6.15
V_USB2: C23.1, C24.1, D9.A, JP15.5V, Q5.1, R17.2, U9.15
V_USB3: C32.1, C33.1, D13.A, JP22.5V, Q7.1, R25.2, U12.15
V_USB4: C41.1, C42.1, D17.A, JP29.5V, Q9.1, R33.2, U15.15
V_USB5: C50.1, C51.1, D21.A, JP36.5V, Q11.1, R41.2, U18.15
V_USB6: C59.1, C60.1, D25.A, JP43.5V, Q13.1, R49.2, U21.15
V_USB7: C68.1, C69.1, D29.A, JP50.5V, Q15.1, R57.2, U24.15
V_USB8: C77.1, C78.1, D33.A, JP57.5V, Q17.1, R65.2, U27.15
V_USB9: C86.1, C87.1, D37.A, JP64.5V, Q19.1, R73.2, U30.15
V_USB10: C95.1, C96.1, D41.A, JP71.5V, Q21.1, R81.2, U33.15
V_USB11: C104.1, C105.1, D45.A, JP78.5V, Q23.1, R89.2, U36.15

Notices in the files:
parts and their libraries:
SparkFun-Capacitors: Licensing: Creative Commons ShareAlike 4.0 International - https://creativecommons.org/licenses/by-sa/4.0
SparkFun-DiscreteSemi: Licensing: CC v3.0 Share-Alike You are welcome to use this library for commercial purposes.
SparkFun-Aesthetics: Released under the Creative Commons
